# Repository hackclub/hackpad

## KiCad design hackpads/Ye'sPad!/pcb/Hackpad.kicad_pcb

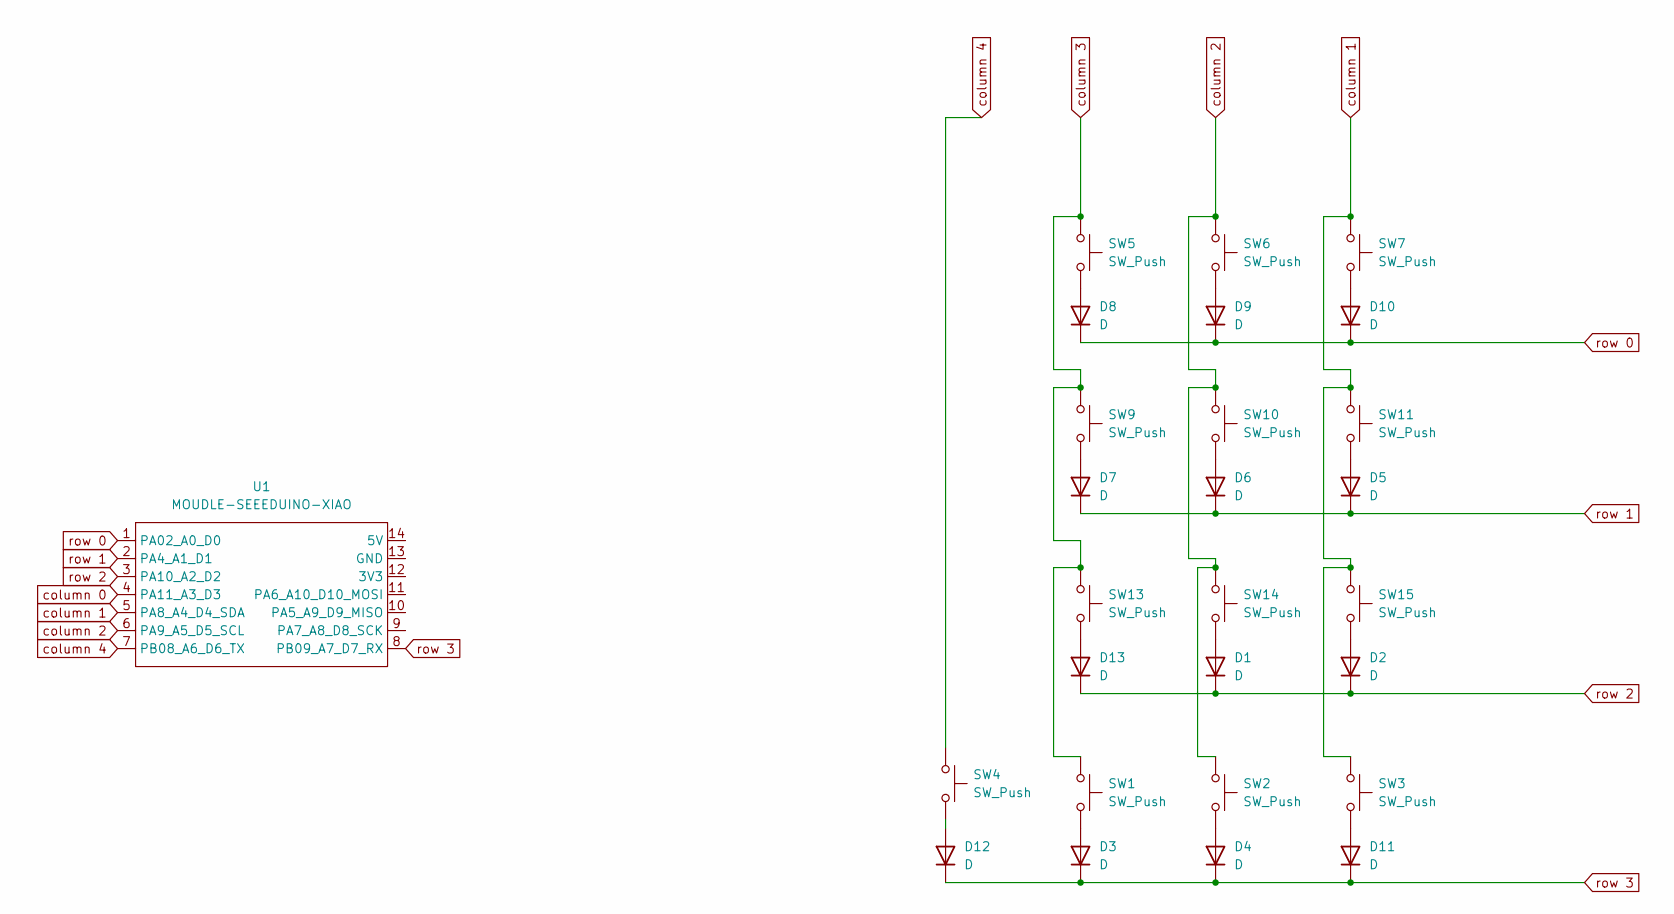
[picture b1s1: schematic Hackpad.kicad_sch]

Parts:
D1, D2, D3, D4, D5, D6, D7, D8, D9, D10, D11, D12, D13: D; 1N4148
SW1, SW2, SW3, SW4, SW5, SW6, SW7, SW9, SW10, SW11, SW13, SW14, SW15: SW_Push; MX-Solderable-1U
U1: MOUDLE-SEEEDUINO-XIAO; XIAO-Generic-Hybrid-14P-2.54-21X17.8MM

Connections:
unnamed: D1.2 (A), SW14.2
unnamed: D2.2 (A), SW15.2
unnamed: D3.2 (A), SW1.2
unnamed: D4.2 (A), SW2.2
unnamed: D5.2 (A), SW11.2
unnamed: D6.2 (A), SW10.2
unnamed: D7.2 (A), SW9.2
unnamed: D8.2 (A), SW5.2
unnamed: D9.2 (A), SW6.2
unnamed: D10.2 (A), SW7.2
unnamed: D11.2 (A), SW3.2
unnamed: D12.2 (A), SW4.2
unnamed: D13.2 (A), SW13.2
column 0: U1.4 (PA11_A3_D3)
column 1: SW3.1, SW7.1, SW11.1, SW15.1, U1.5 (PA8_A4_D4_SDA)
column 2: SW2.1, SW6.1, SW10.1, SW14.1, U1.6 (PA9_A5_D5_SCL)
column 3: SW1.1, SW5.1, SW9.1, SW13.1
column 4: SW4.1, U1.7 (PB08_A6_D6_TX)
row 0: D8.1 (K), D9.1 (K), D10.1 (K), U1.1 (PA02_A0_D0)
row 1: D5.1 (K), D6.1 (K), D7.1 (K), U1.2 (PA4_A1_D1)
row 2: D1.1 (K), D2.1 (K), D13.1 (K), U1.3 (PA10_A2_D2)
row 3: D3.1 (K), D4.1 (K), D11.1 (K), D12.1 (K), U1.8 (PB09_A7_D7_RX)

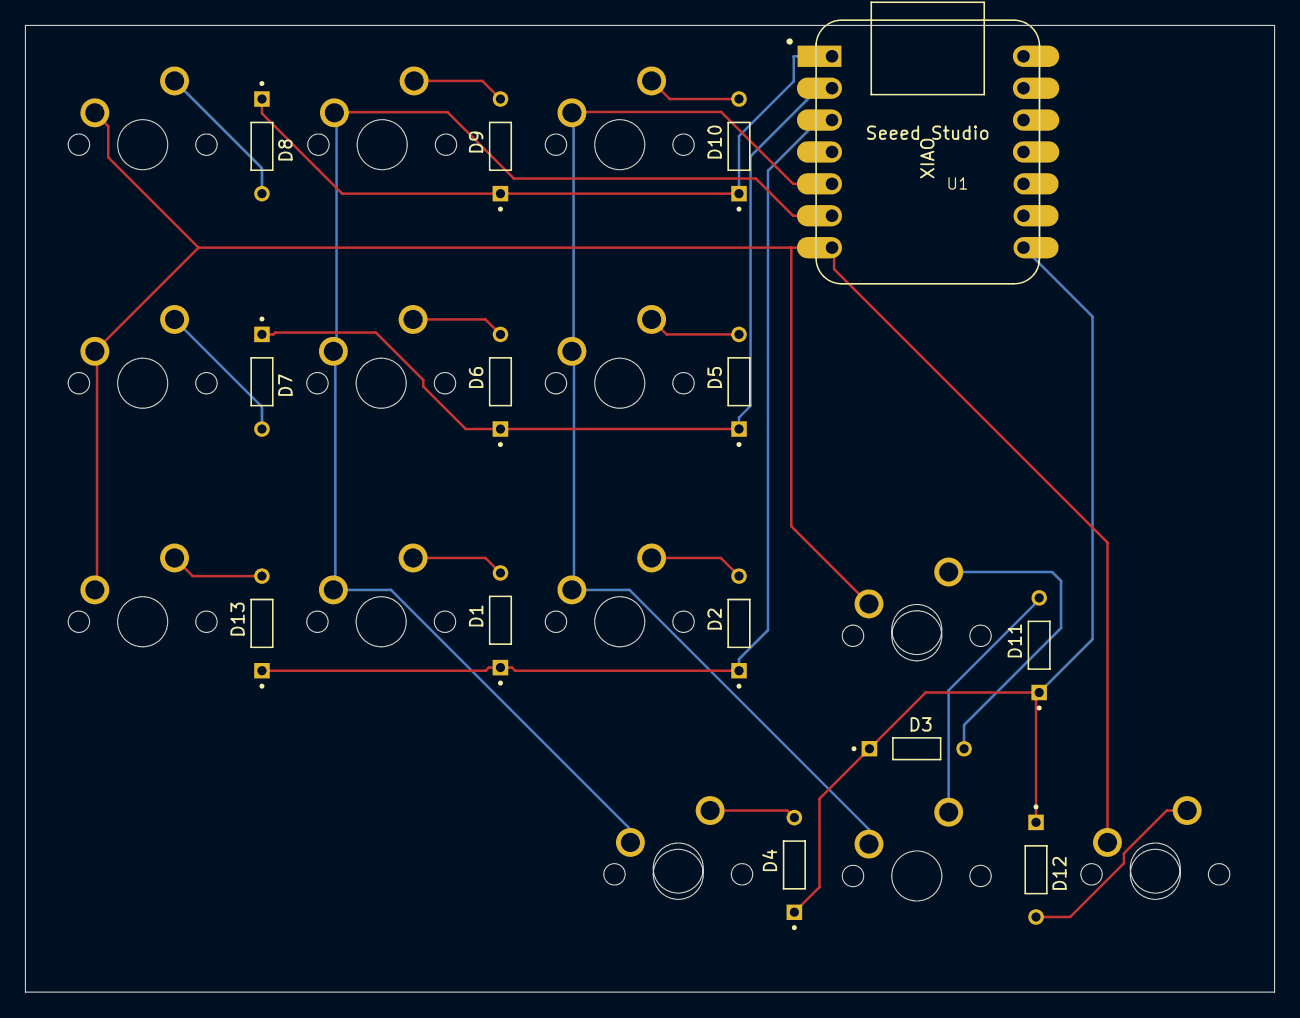
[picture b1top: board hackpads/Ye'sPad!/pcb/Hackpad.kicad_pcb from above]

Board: 2 copper layers, 99.5 x 77.0 mm, 27 parts (0 on the bottom side), 21 nets.

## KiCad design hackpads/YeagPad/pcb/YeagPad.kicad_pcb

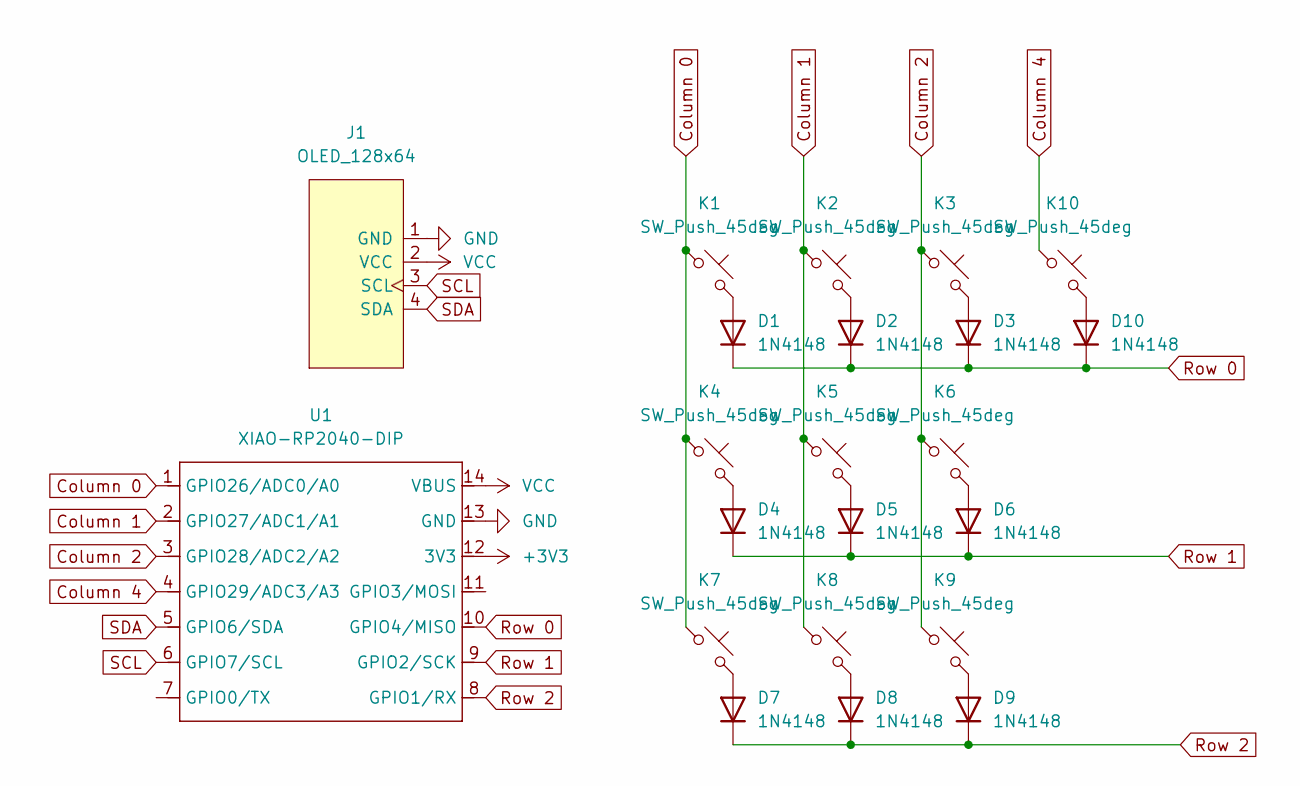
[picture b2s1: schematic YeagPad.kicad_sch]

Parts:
D1, D2, D3, D4, D5, D6, D7, D8, D9, D10: 1N4148; D_DO-35_SOD27_P7.62mm_Horizontal
J1: OLED_128x64
K1, K2, K3, K4, K5, K6, K7, K8, K9, K10: SW_Push_45deg; MX_PCB_1.00u
U1: XIAO-RP2040-DIP; Seeed_XIAO_RP2040

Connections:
+3V3: U1.12 (3V3)
Column 0: K1.1, K4.1, K7.1, U1.1 (GPIO26/ADC0/A0)
Column 1: K2.1, K5.1, K8.1, U1.2 (GPIO27/ADC1/A1)
Column 2: K3.1, K6.1, K9.1, U1.3 (GPIO28/ADC2/A2)
Column 4: K10.1, U1.4 (GPIO29/ADC3/A3)
GND: J1.1 (GND), U1.13 (GND)
unnamed: D1.2 (A), K1.2
unnamed: D2.2 (A), K2.2
unnamed: D3.2 (A), K3.2
unnamed: D4.2 (A), K4.2
unnamed: D5.2 (A), K5.2
unnamed: D6.2 (A), K6.2
unnamed: D7.2 (A), K7.2
unnamed: D8.2 (A), K8.2
unnamed: D9.2 (A), K9.2
unnamed: D10.2 (A), K10.2
Row 0: D1.1 (K), D2.1 (K), D3.1 (K), D10.1 (K), U1.10 (GPIO4/MISO)
Row 1: D4.1 (K), D5.1 (K), D6.1 (K), U1.9 (GPIO2/SCK)
Row 2: D7.1 (K), D8.1 (K), D9.1 (K), U1.8 (GPIO1/RX)
SCL: J1.3 (SCL), U1.6 (GPIO7/SCL)
SDA: J1.4 (SDA), U1.5 (GPIO6/SDA)
VCC: J1.2 (VCC), U1.14 (VBUS)

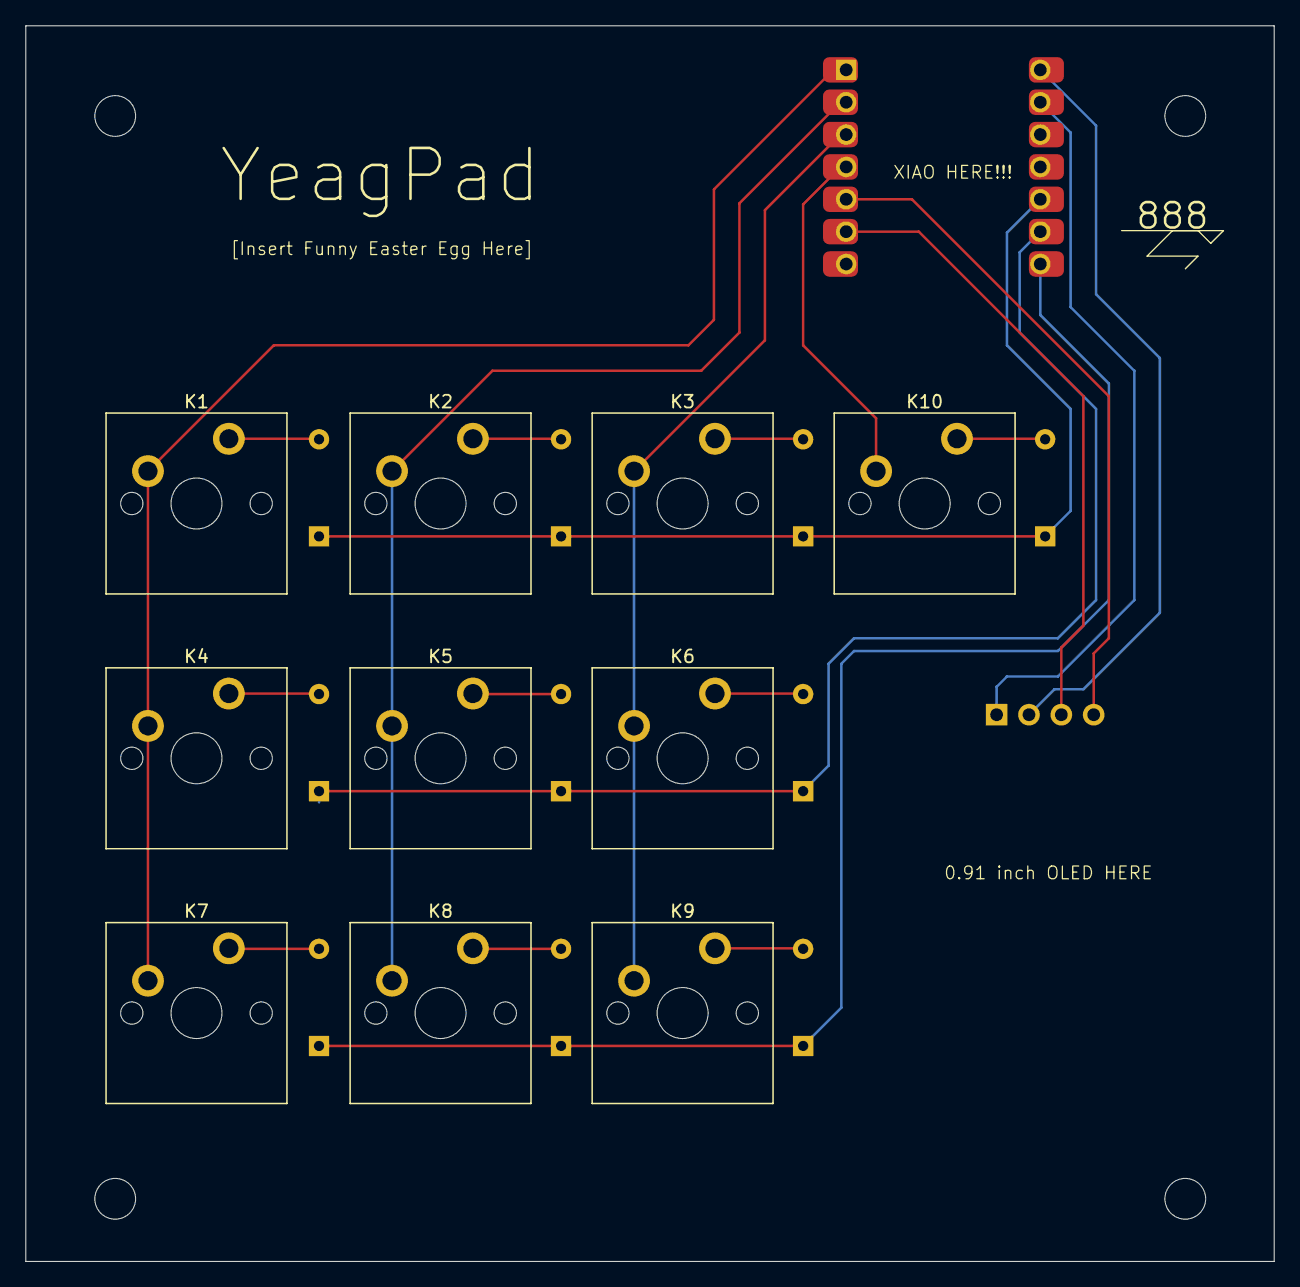
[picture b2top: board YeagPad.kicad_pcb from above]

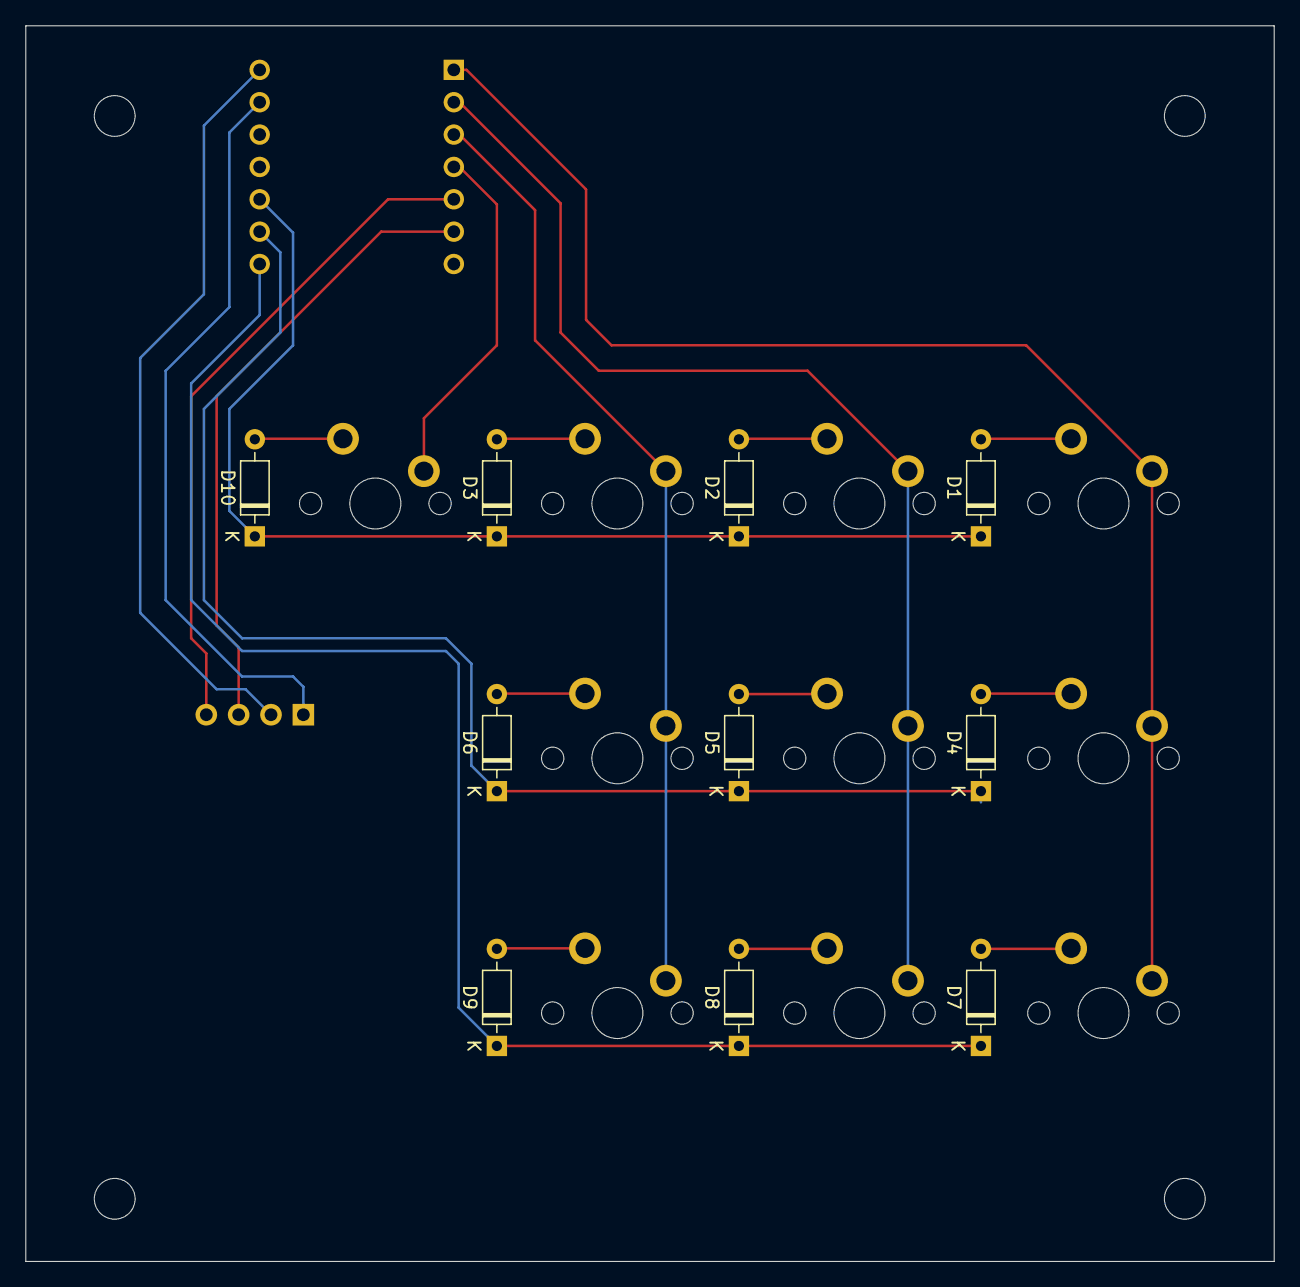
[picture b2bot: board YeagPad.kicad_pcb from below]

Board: 2 copper layers, 98.0 x 97.0 mm, 22 parts (10 on the bottom side), 21 nets.

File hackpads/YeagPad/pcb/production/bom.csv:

Designator,Footprint,Quantity,Value,LCSC Part #
"D1, D10, D2, D3, D4, D5, D6, D7, D8, D9",D_DO-35_SOD27_P7.62mm_Horizontal,10,1N4148,
J1,OLED_128x64,1,OLED_128x64,
"K1, K10, K2, K3, K4, K5, K6, K7, K8, K9",MX_PCB_1.00u,10,SW_Push_45deg,
U1,Seeed_XIAO_RP2040,1,XIAO-RP2040-DIP,

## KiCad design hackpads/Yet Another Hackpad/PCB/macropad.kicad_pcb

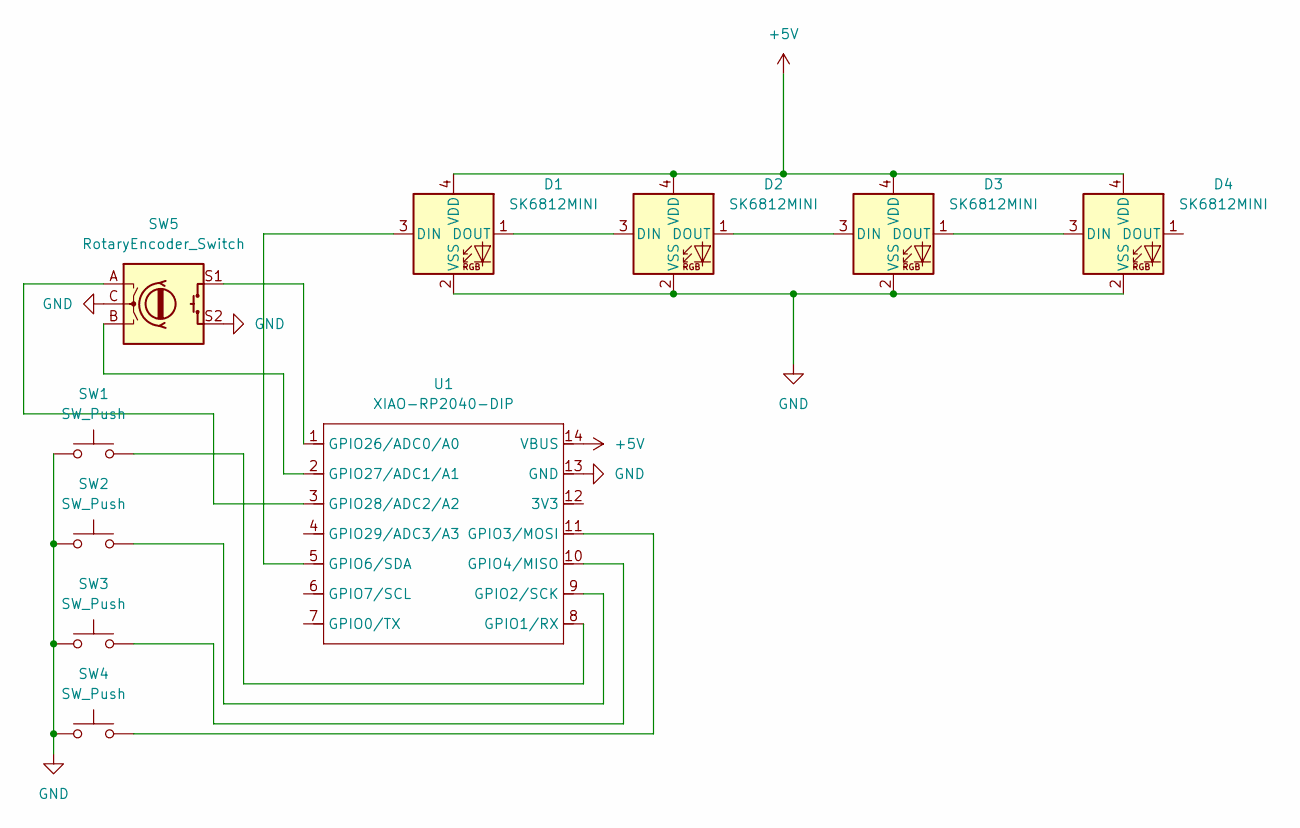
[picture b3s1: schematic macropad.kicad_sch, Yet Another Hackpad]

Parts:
D1, D2, D3, D4: SK6812MINI; SK6812MINI-E
SW1, SW2, SW3, SW4: SW_Push; SW_Cherry_MX_1.00u_PCB
SW5: RotaryEncoder_Switch; RotaryEncoder_Alps_EC11E-Switch_Vertical_H20mm_CircularMoun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
U1: XIAO-RP2040-DIP

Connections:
+5V: D1.4 (VDD), D2.4 (VDD), D3.4 (VDD), D4.4 (VDD), U1.14 (VBUS)
GND: D1.2 (VSS), D2.2 (VSS), D3.2 (VSS), D4.2 (VSS), SW1.1, SW2.1, SW3.1, SW4.1, SW5.C, SW5.S2, U1.13 (GND)
unnamed: D1.3 (DIN), U1.5 (GPIO6/SDA)
unnamed: D1.1 (DOUT), D2.3 (DIN)
unnamed: D2.1 (DOUT), D3.3 (DIN)
unnamed: D3.1 (DOUT), D4.3 (DIN)
unnamed: SW1.2, U1.8 (GPIO1/RX)
unnamed: SW2.2, U1.9 (GPIO2/SCK)
unnamed: SW4.2, U1.11 (GPIO3/MOSI)
unnamed: SW3.2, U1.10 (GPIO4/MISO)
unnamed: SW5.S1, U1.1 (GPIO26/ADC0/A0)
unnamed: SW5.B, U1.2 (GPIO27/ADC1/A1)
unnamed: SW5.A, U1.3 (GPIO28/ADC2/A2)

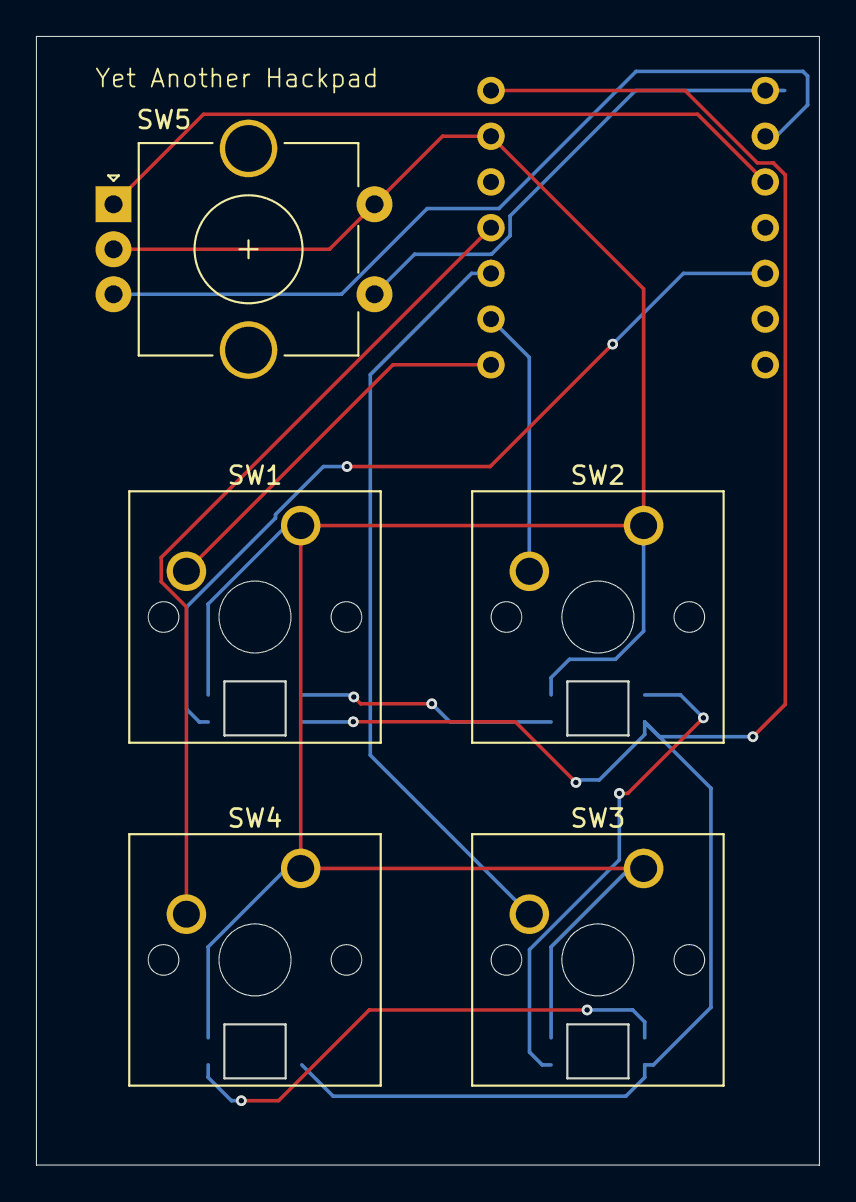
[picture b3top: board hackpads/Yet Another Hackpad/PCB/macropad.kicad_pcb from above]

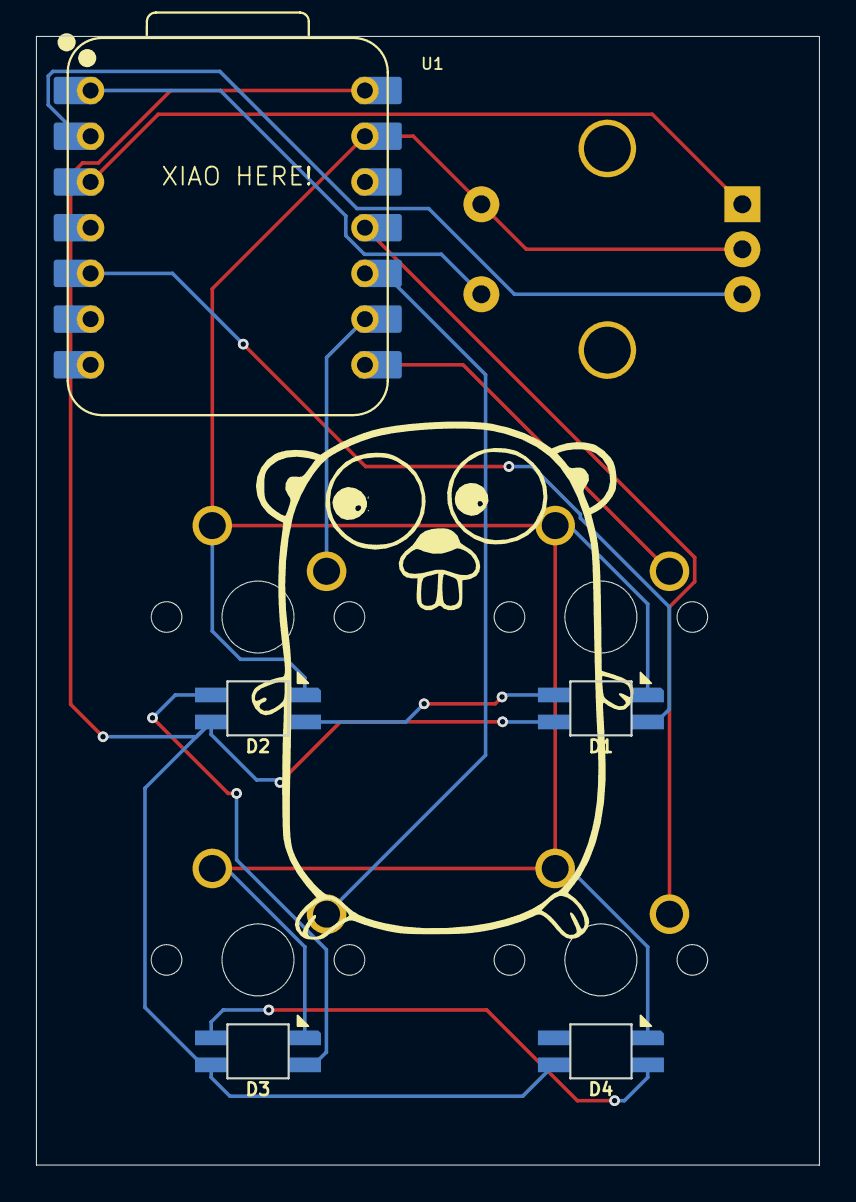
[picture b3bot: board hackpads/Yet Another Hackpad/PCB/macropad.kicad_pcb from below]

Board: 2 copper layers, 43.5 x 62.7 mm, 10 parts (5 on the bottom side), 13 nets.

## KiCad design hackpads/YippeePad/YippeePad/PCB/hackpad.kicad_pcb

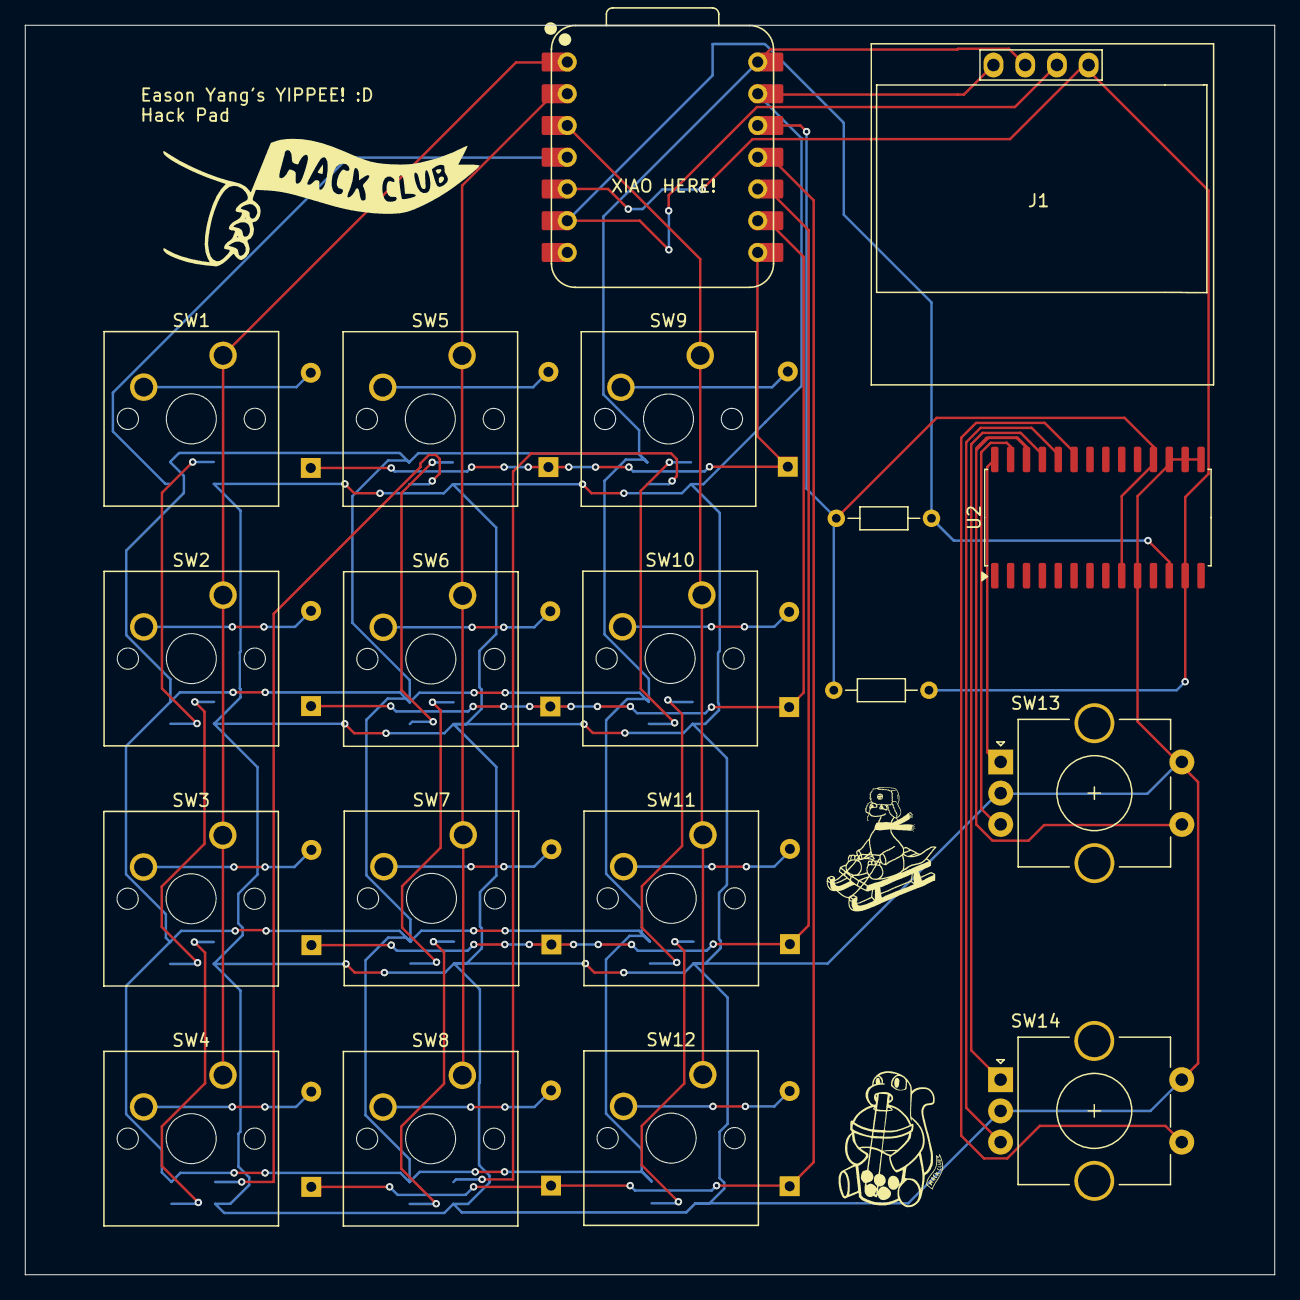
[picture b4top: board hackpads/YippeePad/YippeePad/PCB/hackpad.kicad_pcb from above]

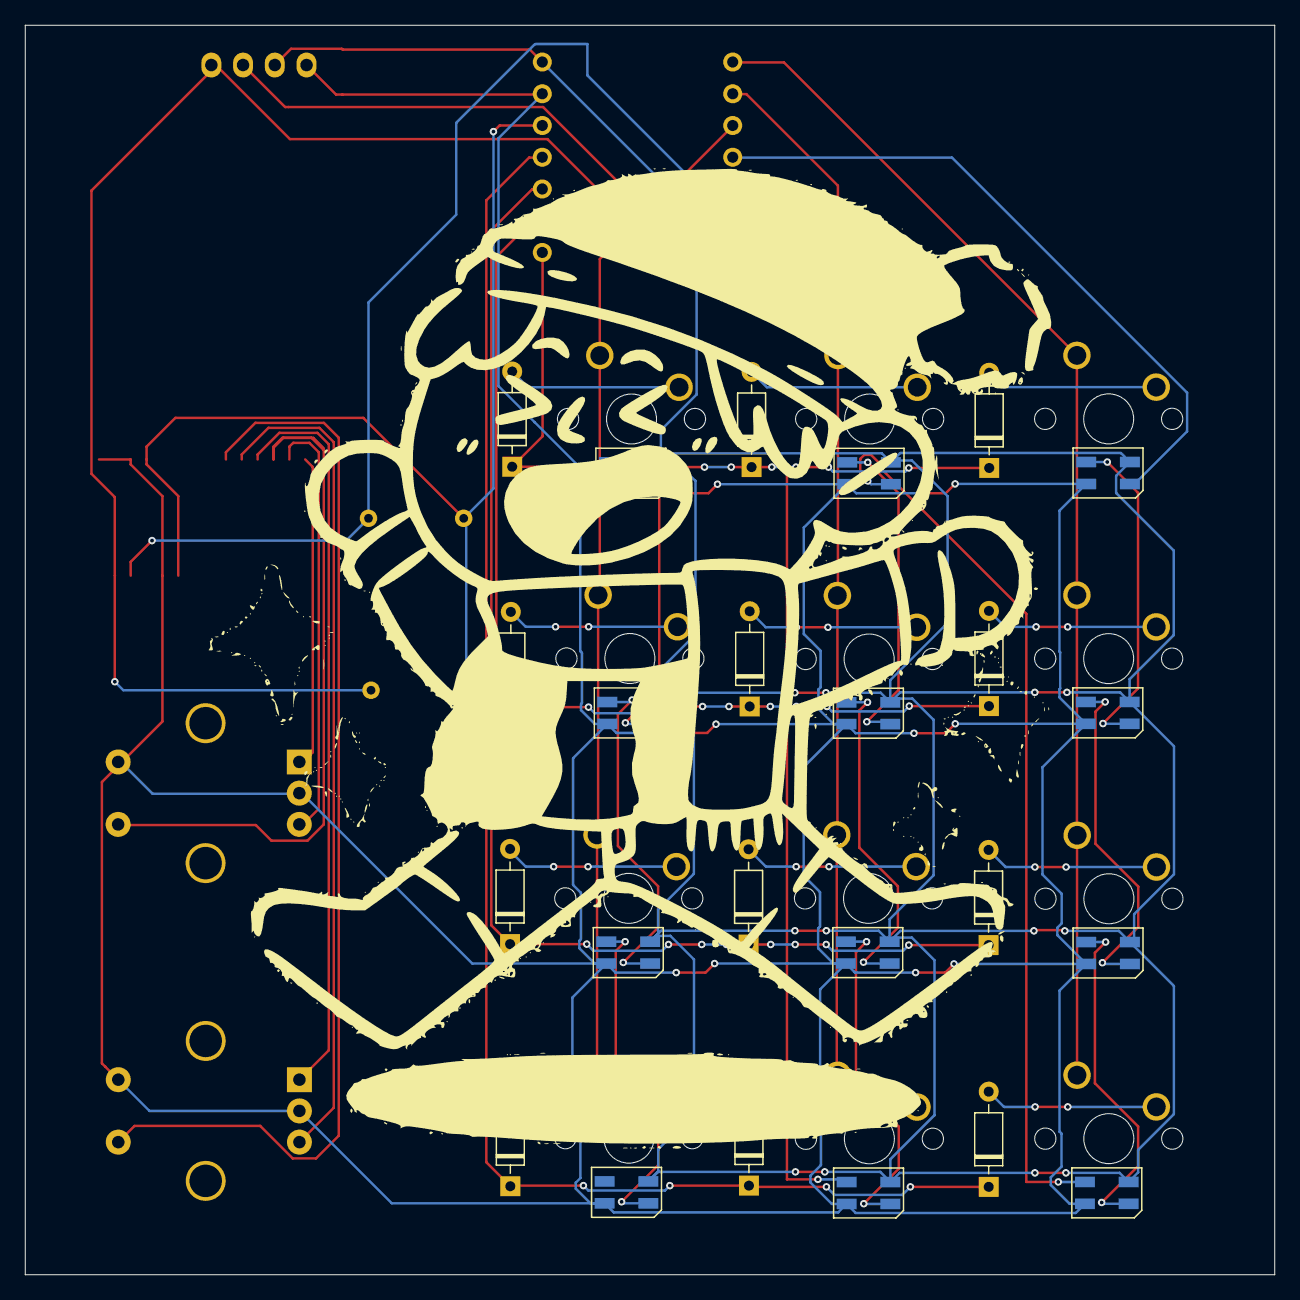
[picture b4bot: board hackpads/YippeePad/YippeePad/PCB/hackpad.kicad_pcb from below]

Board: 2 copper layers, 100.0 x 100.0 mm, 43 parts (24 on the bottom side), 42 nets.

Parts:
D1, D2, D3, D4, D5, D6, D7, D8, D9, D10, D11, D12: 1N4148; D_DO-35_SOD27_P7.62mm_Horizontal
D13, D14, D15, D16, D17, D18, D19, D20, D21, D22, D23, D24: SK6812MINI; LED_SK6812MINI_PLCC4_3.5x3.5mm_P1.75mm
J1: Conn_01x04_Pin; 128x64OLED
R1, R2: R; R_Axial_DIN0204_L3.6mm_D1.6mm_P7.62mm_Horizontal
SW1, SW2, SW3, SW4, SW5, SW6, SW7, SW8, SW9, SW10, SW11, SW12: SW_Push; SW_Cherry_MX_1.00u_PCB
SW13, SW14: RotaryEncoder_Switch; RotaryEncoder_Alps_EC11E-Switch_Vertical_H20mm_CircularMoun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
U1: XIAO-RP2040-DIP
U2: MCP23017_SO; SOIC-28W_7.5x17.9mm_P1.27mm

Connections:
+3.3V: R1.2, R2.2, U1.12 (3V3), U2.9 (VDD), U2.18 (~RESET)
+5V: D13.4 (VDD), D14.4 (VDD), D15.4 (VDD), D16.4 (VDD), D17.4 (VDD), D18.4 (VDD), D19.4 (VDD), D20.4 (VDD), D21.4 (VDD), D22.4 (VDD), D23.4 (VDD), D24.4 (VDD), J1.2, U1.14 (VBUS)
E1_A: SW13.A, U2.28 (GPA7)
E1_B: SW13.B, U2.27 (GPA6)
E1_SW: SW13.S1, U2.26 (GPA5)
E2_A: SW14.A, U2.25 (GPA4)
E2_B: SW14.B, U2.24 (GPA3)
E2_SW: SW14.S1, U2.23 (GPA2)
GND: D13.2 (VSS), D14.2 (VSS), D15.2 (VSS), D16.2 (VSS), D17.2 (VSS), D18.2 (VSS), D19.2 (VSS), D20.2 (VSS), D21.2 (VSS), D22.2 (VSS), D23.2 (VSS), D24.2 (VSS), J1.1, SW13.C, SW13.S2, SW14.C, SW14.S2, U1.13 (GND), U2.10 (VSS), U2.15 (A0), U2.16 (A1), U2.17 (A2)
LED: D13.3 (DIN), U1.4 (GPIO29/ADC3/A3)
unnamed: D1.2 (A), SW1.2
unnamed: D2.2 (A), SW2.2
unnamed: D3.2 (A), SW3.2
unnamed: D4.2 (A), SW4.2
unnamed: D5.2 (A), SW5.2
unnamed: D6.2 (A), SW6.2
unnamed: D7.2 (A), SW7.2
unnamed: D8.2 (A), SW8.2
unnamed: D9.2 (A), SW9.2
unnamed: D10.2 (A), SW10.2
unnamed: D11.2 (A), SW11.2
unnamed: D12.2 (A), SW12.2
unnamed: D13.1 (DOUT), D14.3 (DIN)
unnamed: D14.1 (DOUT), D15.3 (DIN)
unnamed: D15.1 (DOUT), D16.3 (DIN)
unnamed: D16.1 (DOUT), D17.3 (DIN)
unnamed: D17.1 (DOUT), D18.3 (DIN)
unnamed: D18.1 (DOUT), D19.3 (DIN)
unnamed: D19.1 (DOUT), D20.3 (DIN)
unnamed: D20.1 (DOUT), D21.3 (DIN)
unnamed: D21.1 (DOUT), D22.3 (DIN)
unnamed: D22.1 (DOUT), D23.3 (DIN)
unnamed: D23.1 (DOUT), D24.3 (DIN)
unnamed: J1.3, R1.1, U1.6 (GPIO7/SCL), U2.12 (SCK)
unnamed: J1.4, R2.1, U1.5 (GPIO6/SDA), U2.13 (SDA)
column 1: SW1.1, SW2.1, SW3.1, SW4.1, U1.1 (GPIO26/ADC0/A0)
column 2: SW5.1, SW6.1, SW7.1, SW8.1, U1.2 (GPIO27/ADC1/A1)
column 3: SW9.1, SW10.1, SW11.1, SW12.1, U1.3 (GPIO28/ADC2/A2)
row 1: D1.1 (K), D5.1 (K), D9.1 (K), U1.8 (GPIO1/RX)
row 2: D2.1 (K), D6.1 (K), D10.1 (K), U1.9 (GPIO2/SCK)
row 3: D3.1 (K), D7.1 (K), D11.1 (K), U1.10 (GPIO4/MISO)
row 4: D4.1 (K), D8.1 (K), D12.1 (K), U1.11 (GPIO3/MOSI)

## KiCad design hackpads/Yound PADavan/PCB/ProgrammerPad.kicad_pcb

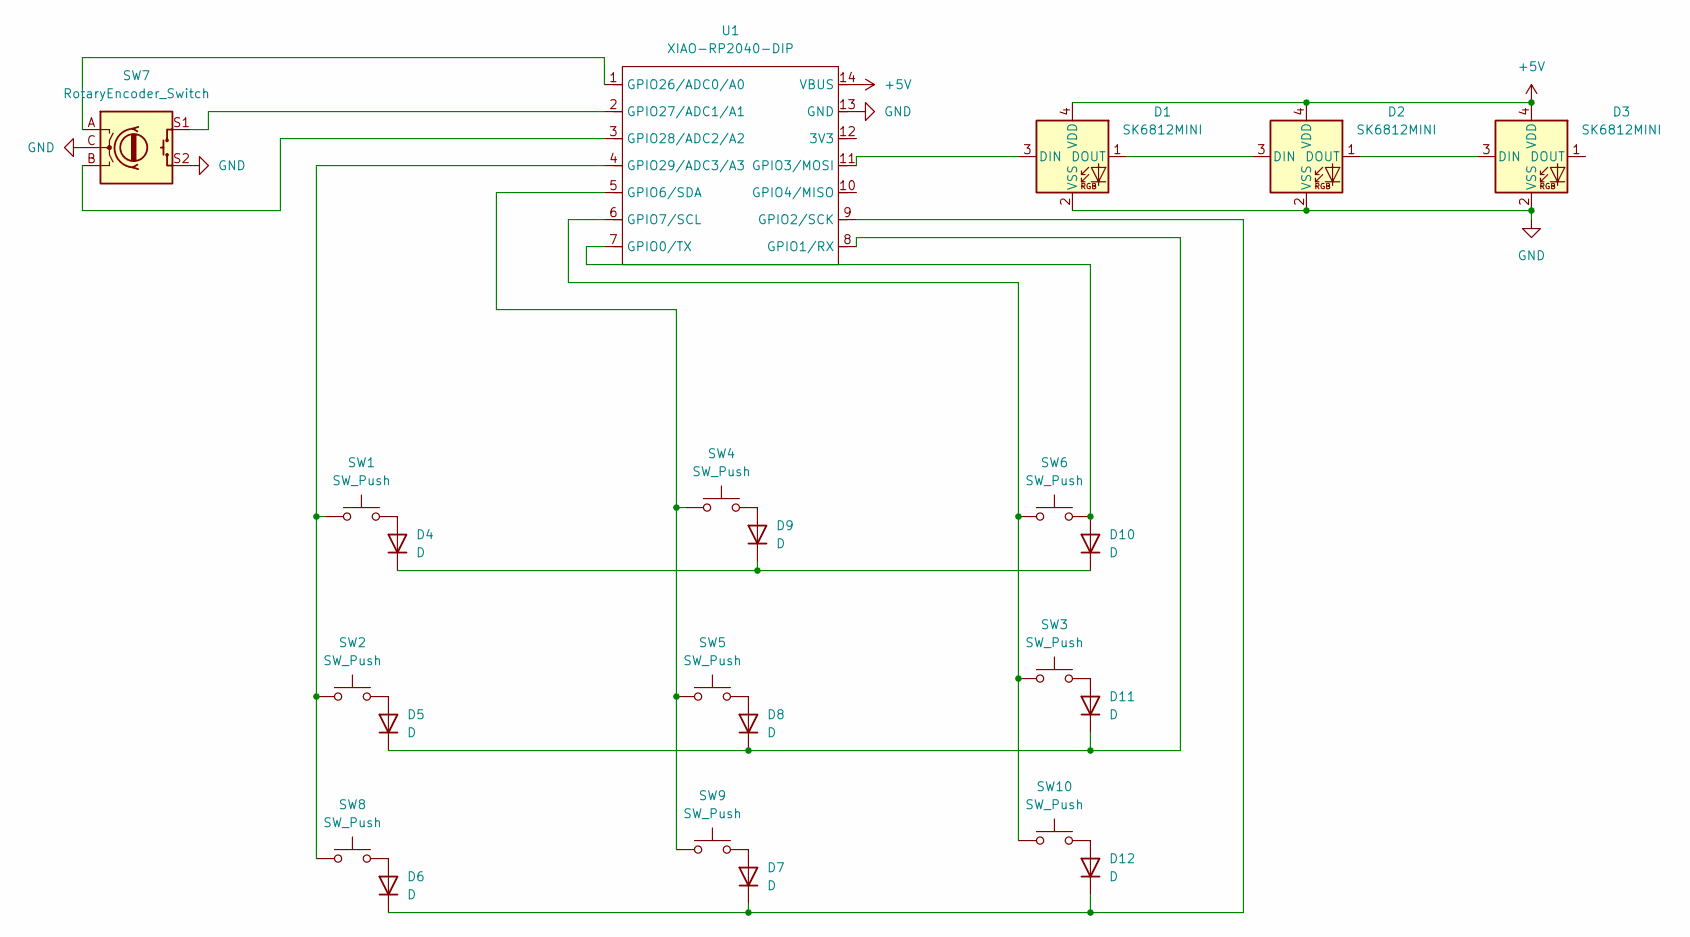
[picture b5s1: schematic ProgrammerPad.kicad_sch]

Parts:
D1, D2, D3: SK6812MINI; LED_SK6812MINI_PLCC4_3.5x3.5mm_P1.75mm
D4, D5, D6, D7, D8, D9, D10, D11, D12: D; D_DO-35_SOD27_P7.62mm_Horizontal
SW1, SW2, SW3, SW4, SW5, SW6, SW8, SW9, SW10: SW_Push; SW_Cherry_MX_1.00u_PCB
SW7: RotaryEncoder_Switch; RotaryEncoder_Alps_EC11E-Switch_Vertical_H20mm_CircularMoun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
U1: XIAO-RP2040-DIP

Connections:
+5V: D1.4 (VDD), D2.4 (VDD), D3.4 (VDD), U1.14 (VBUS)
GND: D1.2 (VSS), D2.2 (VSS), D3.2 (VSS), SW7.C, SW7.S2, U1.13 (GND)
unnamed: D1.3 (DIN), U1.11 (GPIO3/MOSI)
unnamed: D1.1 (DOUT), D2.3 (DIN)
unnamed: D2.1 (DOUT), D3.3 (DIN)
unnamed: D4.2 (A), SW1.2
unnamed: D5.2 (A), SW2.2
unnamed: D6.2 (A), SW8.2
unnamed: D7.2 (A), SW9.2
unnamed: D8.2 (A), SW5.2
unnamed: D9.2 (A), SW4.2
unnamed: D10.2 (A), SW6.2, U1.7 (GPIO0/TX)
unnamed: D4.1 (K), D9.1 (K), D10.1 (K)
unnamed: D11.2 (A), SW3.2
unnamed: D5.1 (K), D8.1 (K), D11.1 (K), U1.8 (GPIO1/RX)
unnamed: D12.2 (A), SW10.2
unnamed: D6.1 (K), D7.1 (K), D12.1 (K), U1.9 (GPIO2/SCK)
unnamed: SW4.1, SW5.1, SW9.1, U1.5 (GPIO6/SDA)
unnamed: SW3.1, SW6.1, SW10.1, U1.6 (GPIO7/SCL)
unnamed: SW7.A, U1.1 (GPIO26/ADC0/A0)
unnamed: SW7.S1, U1.2 (GPIO27/ADC1/A1)
unnamed: SW7.B, U1.3 (GPIO28/ADC2/A2)
unnamed: SW1.1, SW2.1, SW8.1, U1.4 (GPIO29/ADC3/A3)

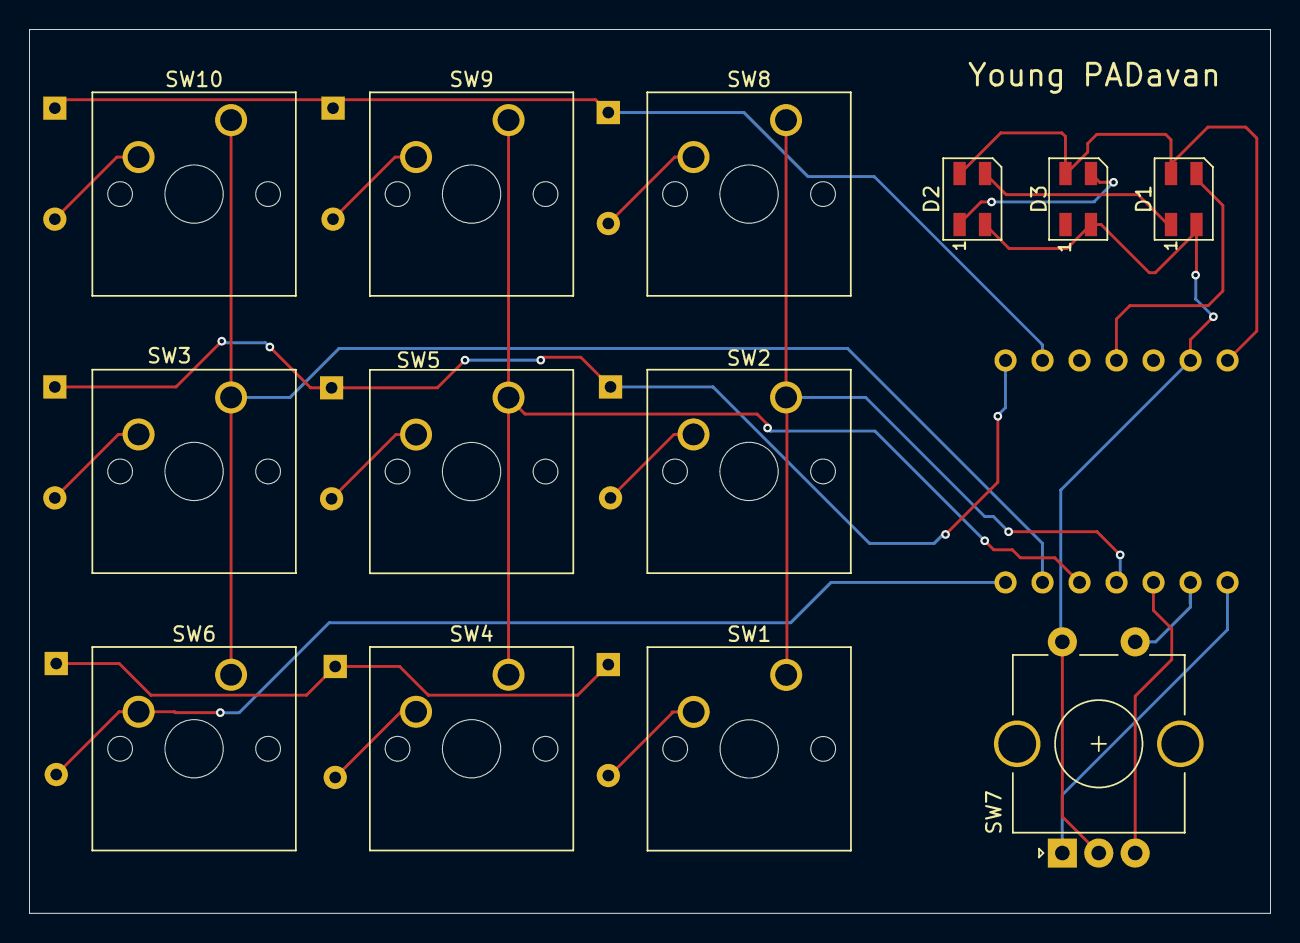
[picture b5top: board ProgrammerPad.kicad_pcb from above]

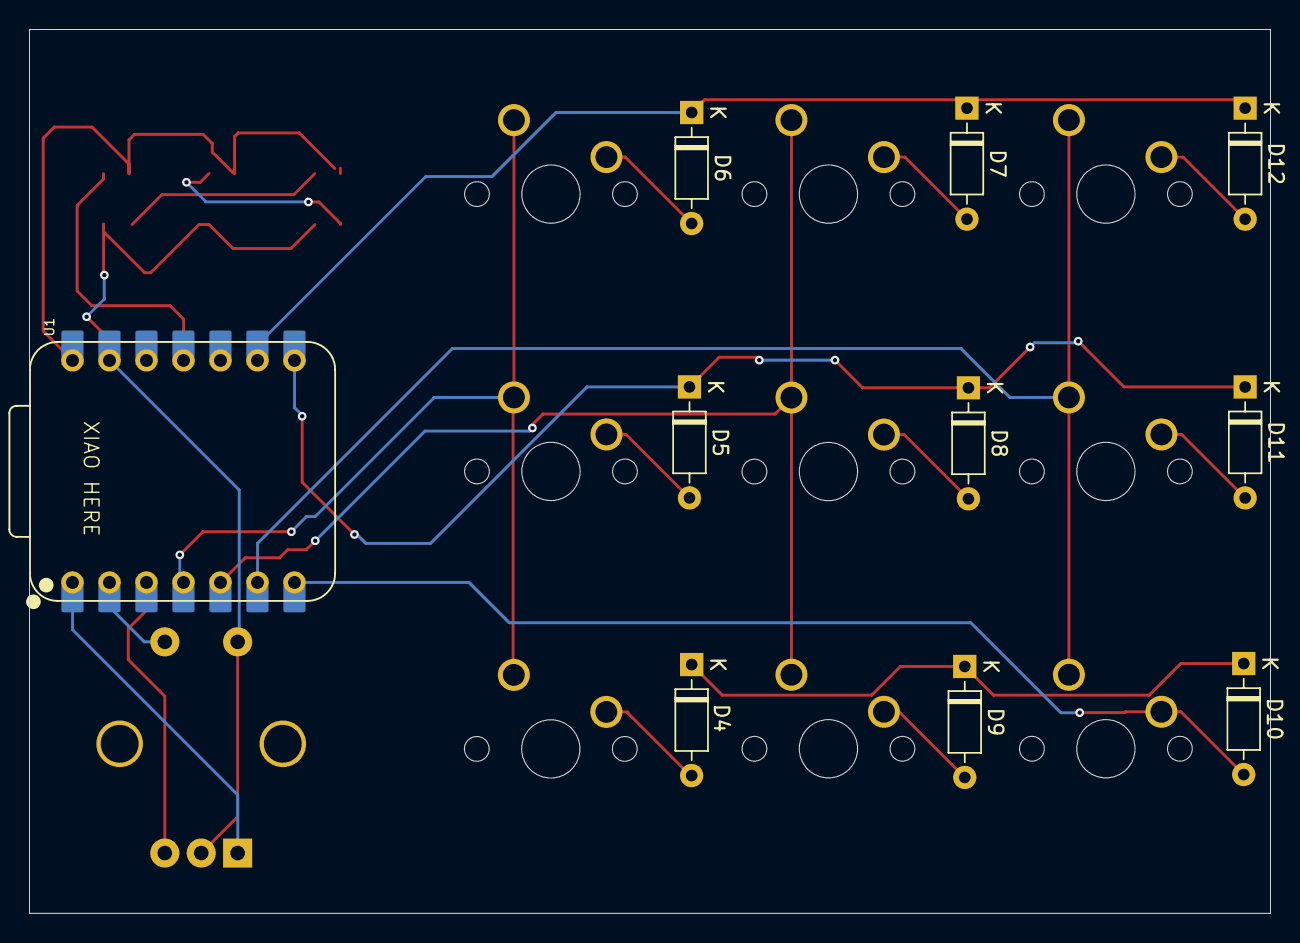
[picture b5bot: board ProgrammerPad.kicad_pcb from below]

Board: 2 copper layers, 85.2 x 60.7 mm, 23 parts (10 on the bottom side), 23 nets.
